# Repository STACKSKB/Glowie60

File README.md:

A Bakeneko60 PCB with RGB underglow LEDs

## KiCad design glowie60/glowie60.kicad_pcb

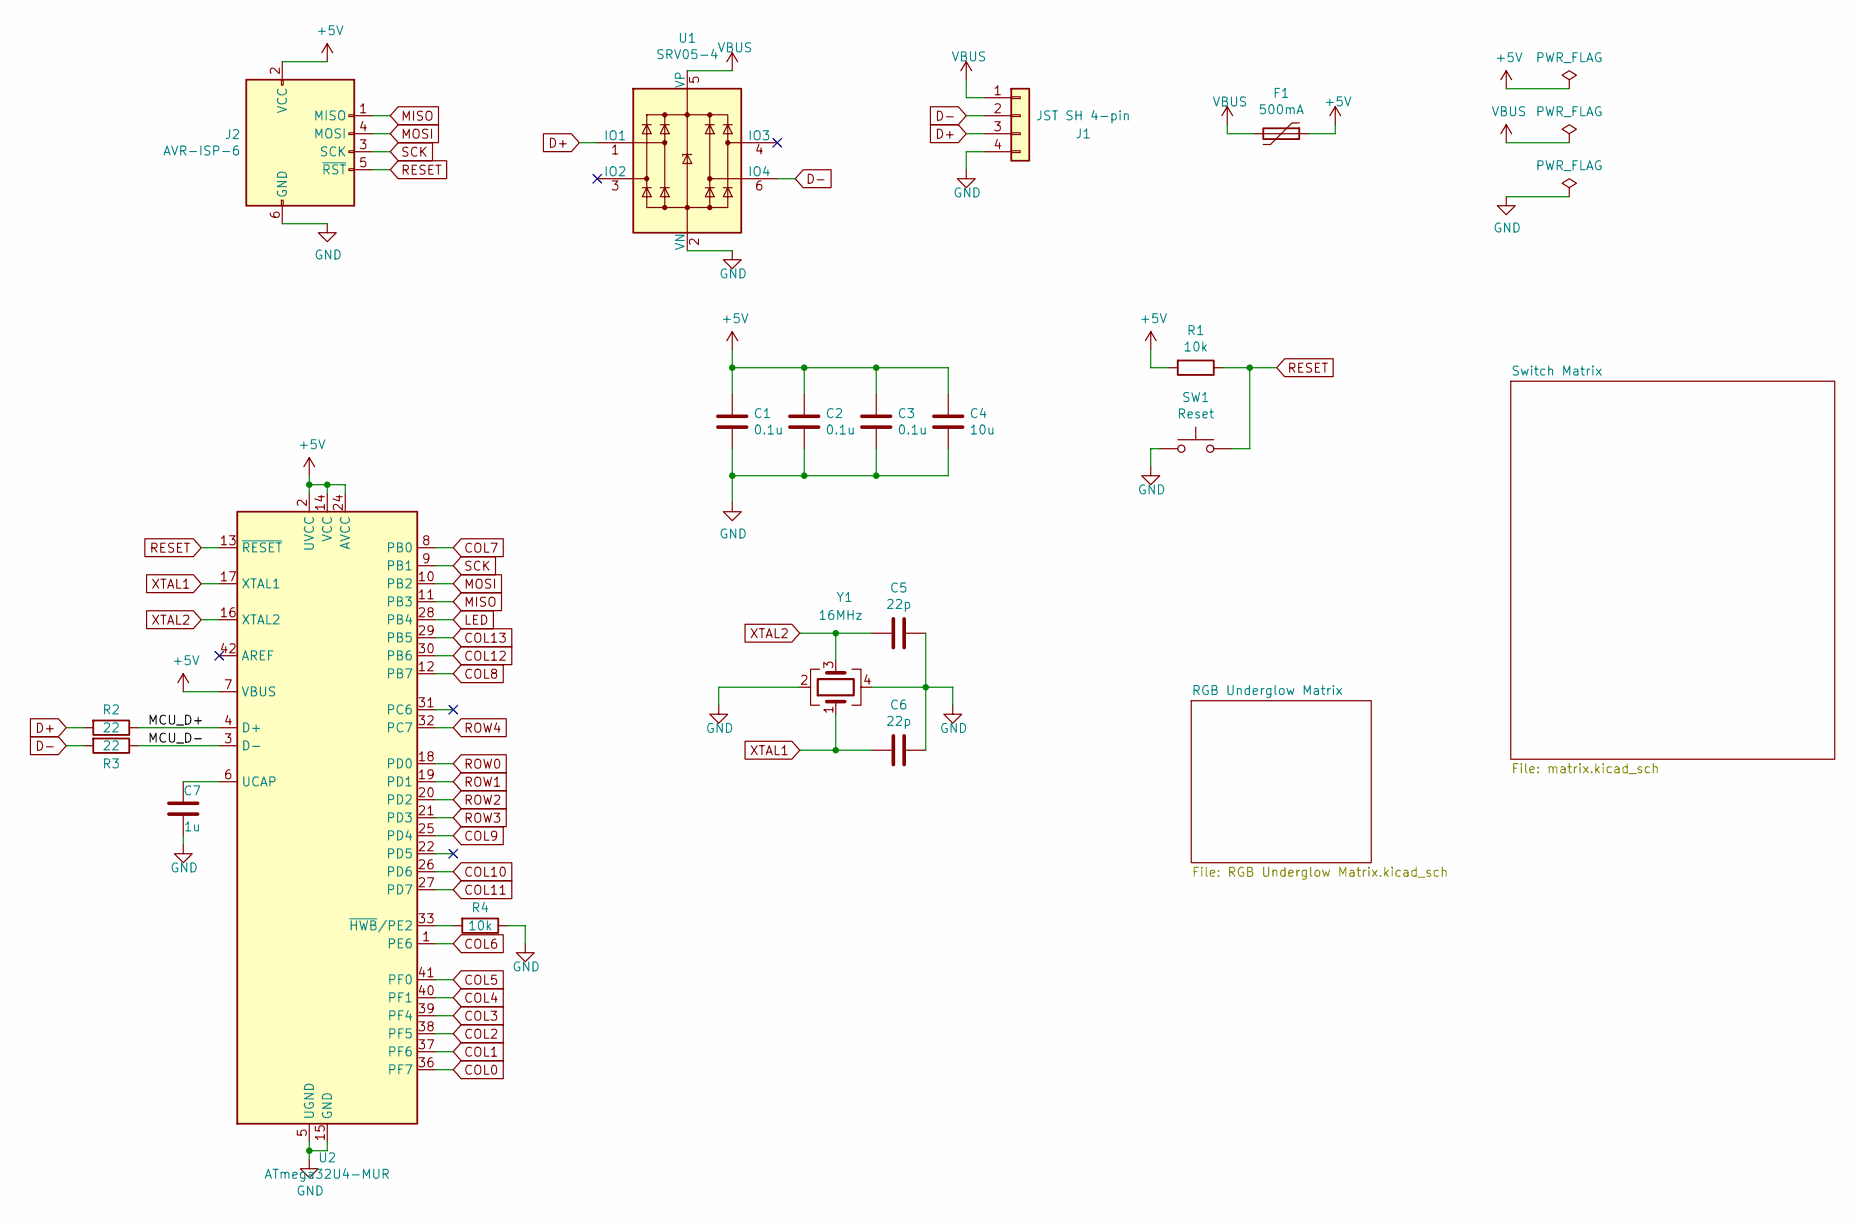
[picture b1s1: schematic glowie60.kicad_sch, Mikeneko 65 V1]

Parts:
C1, C2, C3: 0.1u; C_0805_2012Metric; LCSC Part # C49678
C4: 10u; C_0805_2012Metric; LCSC Part # C15850
C5, C6: 22p; C_0805_2012Metric; LCSC Part # C1804
C7: 1u; C_0805_2012Metric; LCSC Part # C28323
F1: 500mA; Fuse_1206_3216Metric; LCSC Part # C70076
J1: JST SH 4-pin; JST_SH_SM04B-SRSS-TB_1x04-1MP_P1.00mm_Horizontal; LCSC Part # C145956
J2: AVR-ISP-6; ISP
R1, R4: 10k; R_0805_2012Metric; LCSC Part # C17414
R2, R3: 22; R_0805_2012Metric; LCSC Part # C17561
SW1: Reset; SW_SPST_TL3342; LCSC Part # C318884
U1: SRV05-4; SOT-23-6; LCSC Part # C85364
U2: ATmega32U4-MUR; QFN-44-1EP_7x7mm_P0.5mm_EP5.2x5.2mm; LCSC Part # C45874
Y1: 16MHz; Crystal_SMD_3225-4Pin_3.2x2.5mm; LCSC Part # C13738

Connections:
/MCU_D+: R2.1, U2.4 (D+)
/MCU_D-: R3.1, U2.3 (D-)
COL0: U2.36 (PF7); also elsewhere on the board
COL1: U2.37 (PF6); also elsewhere on the board
COL2: U2.38 (PF5); also elsewhere on the board
COL3: U2.39 (PF4); also elsewhere on the board
COL4: U2.40 (PF1); also elsewhere on the board
COL5: U2.41 (PF0); also elsewhere on the board
COL6: U2.1 (PE6); also elsewhere on the board
COL7: U2.8 (PB0); also elsewhere on the board
COL8: U2.12 (PB7); also elsewhere on the board
COL9: U2.25 (PD4); also elsewhere on the board
COL10: U2.26 (PD6); also elsewhere on the board
COL11: U2.27 (PD7); also elsewhere on the board
COL12: U2.30 (PB6); also elsewhere on the board
COL13: U2.29 (PB5); also elsewhere on the board
D+: J1.3, R2.2, U1.1 (IO1)
D-: J1.2, R3.2, U1.6 (IO4)
LED: U2.28 (PB4); also elsewhere on the board
MISO: J2.1 (MISO), U2.11 (PB3)
MOSI: J2.4 (MOSI), U2.10 (PB2)
unnamed: C7.1, U2.6 (UCAP)
unnamed: R4.2, U2.33 (~HWB/PE2)
RESET: J2.5 (~RST), R1.1, SW1.2, U2.13 (~RESET)
ROW0: U2.18 (PD0); also elsewhere on the board
ROW1: U2.19 (PD1); also elsewhere on the board
ROW2: U2.20 (PD2); also elsewhere on the board
ROW3: U2.21 (PD3); also elsewhere on the board
ROW4: U2.32 (PC7); also elsewhere on the board
SCK: J2.3 (SCK), U2.9 (PB1)
VBUS: F1.2, J1.1, U1.5 (VP)
XTAL1: C6.2, U2.17 (XTAL1), Y1.1
XTAL2: C5.2, U2.16 (XTAL2), Y1.3

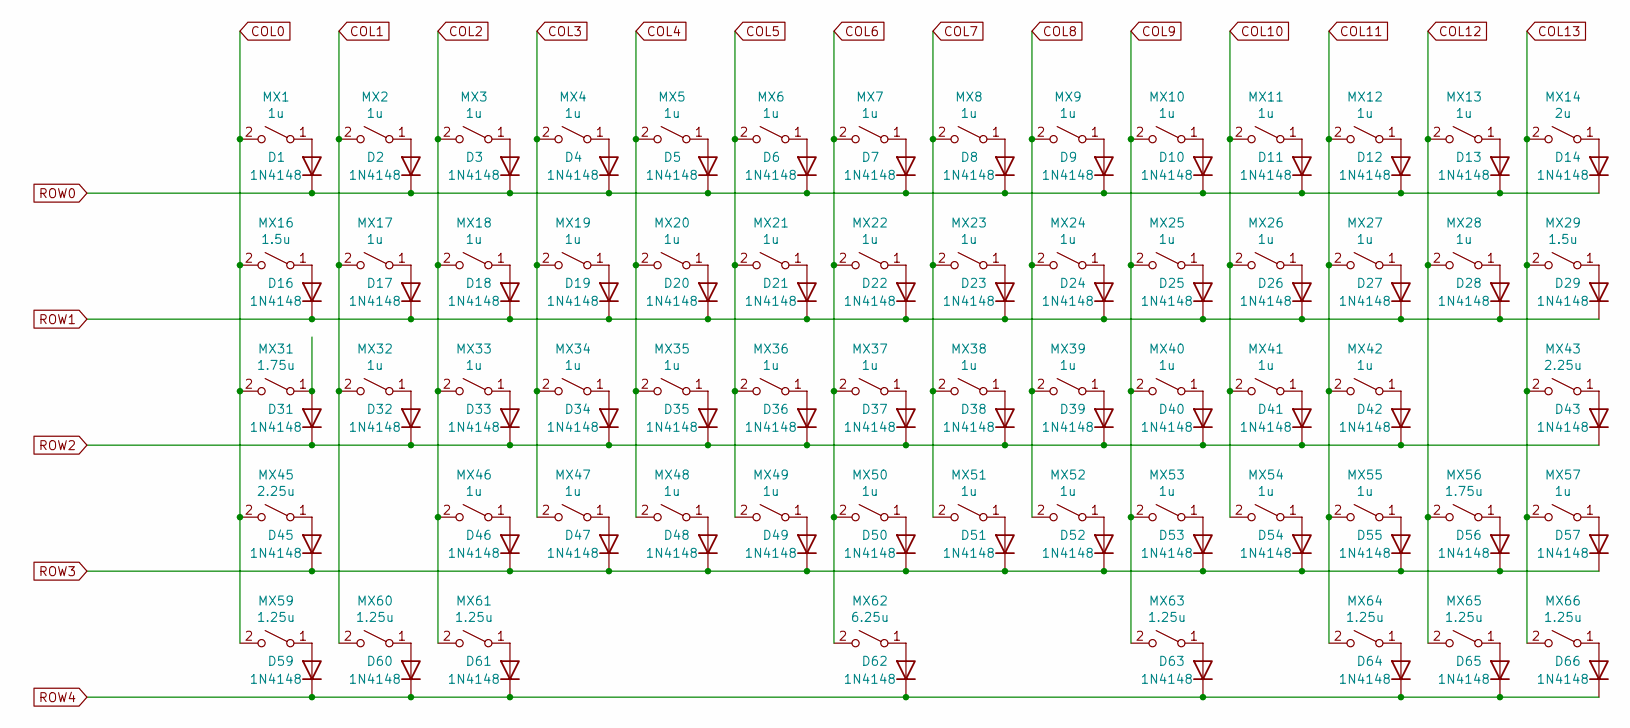
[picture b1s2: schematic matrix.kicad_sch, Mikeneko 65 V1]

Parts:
D1, D2, D3, D4, D5, D6, D7, D8, D9, D10, D11, D12, D13, D14, D16, D17, D18, D19, D20, D21, D22, D23, D24, D25, D26, D27, D28, D29, D31, D32, D33, D34, D35, D36, D37, D38, D39, D40, D41, D42, D43, D45, D46, D47, D48, D49, D50, D51, D52, D53, D54, D55, D56, D57, D59, D60, D61, D62, D63, D64, D65, D66: 1N4148; D_SOD-123; LCSC Part # C81598
MX1, MX2, MX3, MX4, MX5, MX6, MX7, MX8, MX9, MX10, MX11, MX12, MX13, MX17, MX18, MX19, MX20, MX21, MX22, MX23, MX24, MX25, MX26, MX27, MX28, MX32, MX33, MX34, MX35, MX36, MX37, MX38, MX39, MX40, MX41, MX42, MX46, MX47, MX48, MX49, MX50, MX51, MX52, MX53, MX54, MX55, MX57: 1u; MXOnly-1U-Hotswap; LCSC Part # C2803348
MX14: 2u; MXOnly-2U-Hotswap; LCSC Part # C2803348
MX16, MX29: 1.5u; MXOnly-1.5U-Hotswap; LCSC Part # C2803348
MX31, MX56: 1.75u; MXOnly-1.75U-Hotswap; LCSC Part # C2803348
MX43, MX45: 2.25u; MXOnly-2.25U-Hotswap; LCSC Part # C2803348
MX59, MX60, MX61, MX63, MX64, MX65, MX66: 1.25u; MXOnly-1.25U-Hotswap; LCSC Part # C2803348
MX62: 6.25u; MXOnly-6.25U-Hotswap-ReversedStabilizers; LCSC Part # C2803348

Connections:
COL0: MX1.2 (B), MX16.2 (B), MX31.2 (B), MX45.2 (B), MX59.2 (B); also elsewhere on the board
COL1: MX2.2 (B), MX17.2 (B), MX32.2 (B), MX60.2 (B); also elsewhere on the board
COL2: MX3.2 (B), MX18.2 (B), MX33.2 (B), MX46.2 (B), MX61.2 (B); also elsewhere on the board
COL3: MX4.2 (B), MX19.2 (B), MX34.2 (B), MX47.2 (B); also elsewhere on the board
COL4: MX5.2 (B), MX20.2 (B), MX35.2 (B), MX48.2 (B); also elsewhere on the board
COL5: MX6.2 (B), MX21.2 (B), MX36.2 (B), MX49.2 (B); also elsewhere on the board
COL6: MX7.2 (B), MX22.2 (B), MX37.2 (B), MX50.2 (B), MX62.2 (B); also elsewhere on the board
COL7: MX8.2 (B), MX23.2 (B), MX38.2 (B), MX51.2 (B); also elsewhere on the board
COL8: MX9.2 (B), MX24.2 (B), MX39.2 (B), MX52.2 (B); also elsewhere on the board
COL9: MX10.2 (B), MX25.2 (B), MX40.2 (B), MX53.2 (B), MX63.2 (B); also elsewhere on the board
COL10: MX11.2 (B), MX26.2 (B), MX41.2 (B), MX54.2 (B); also elsewhere on the board
COL11: MX12.2 (B), MX27.2 (B), MX42.2 (B), MX55.2 (B), MX64.2 (B); also elsewhere on the board
COL12: MX13.2 (B), MX28.2 (B), MX56.2 (B), MX65.2 (B); also elsewhere on the board
COL13: MX14.2 (B), MX29.2 (B), MX43.2 (B), MX57.2 (B), MX66.2 (B); also elsewhere on the board
unnamed: D1.2 (A), MX1.1 (A)
unnamed: D2.2 (A), MX2.1 (A)
unnamed: D3.2 (A), MX3.1 (A)
unnamed: D4.2 (A), MX4.1 (A)
unnamed: D5.2 (A), MX5.1 (A)
unnamed: D6.2 (A), MX6.1 (A)
unnamed: D7.2 (A), MX7.1 (A)
unnamed: D8.2 (A), MX8.1 (A)
unnamed: D9.2 (A), MX9.1 (A)
unnamed: D10.2 (A), MX10.1 (A)
unnamed: D11.2 (A), MX11.1 (A)
unnamed: D12.2 (A), MX12.1 (A)
unnamed: D13.2 (A), MX13.1 (A)
unnamed: D14.2 (A), MX14.1 (A)
unnamed: D16.2 (A), MX16.1 (A)
unnamed: D17.2 (A), MX17.1 (A)
unnamed: D18.2 (A), MX18.1 (A)
unnamed: D19.2 (A), MX19.1 (A)
unnamed: D20.2 (A), MX20.1 (A)
unnamed: D21.2 (A), MX21.1 (A)
unnamed: D22.2 (A), MX22.1 (A)
unnamed: D23.2 (A), MX23.1 (A)
unnamed: D24.2 (A), MX24.1 (A)
unnamed: D25.2 (A), MX25.1 (A)
unnamed: D26.2 (A), MX26.1 (A)
unnamed: D27.2 (A), MX27.1 (A)
unnamed: D28.2 (A), MX28.1 (A)
unnamed: D29.2 (A), MX29.1 (A)
unnamed: D31.2 (A), MX31.1 (A)
unnamed: D32.2 (A), MX32.1 (A)
unnamed: D33.2 (A), MX33.1 (A)
unnamed: D34.2 (A), MX34.1 (A)
unnamed: D35.2 (A), MX35.1 (A)
unnamed: D36.2 (A), MX36.1 (A)
unnamed: D37.2 (A), MX37.1 (A)
unnamed: D38.2 (A), MX38.1 (A)
unnamed: D39.2 (A), MX39.1 (A)
unnamed: D40.2 (A), MX40.1 (A)
unnamed: D41.2 (A), MX41.1 (A)
unnamed: D42.2 (A), MX42.1 (A)
unnamed: D43.2 (A), MX43.1 (A)
unnamed: D45.2 (A), MX45.1 (A)
unnamed: D46.2 (A), MX46.1 (A)
unnamed: D47.2 (A), MX47.1 (A)
unnamed: D48.2 (A), MX48.1 (A)
unnamed: D49.2 (A), MX49.1 (A)
unnamed: D50.2 (A), MX50.1 (A)
unnamed: D51.2 (A), MX51.1 (A)
unnamed: D52.2 (A), MX52.1 (A)
unnamed: D53.2 (A), MX53.1 (A)
unnamed: D54.2 (A), MX54.1 (A)
unnamed: D55.2 (A), MX55.1 (A)
unnamed: D56.2 (A), MX56.1 (A)
unnamed: D57.2 (A), MX57.1 (A)
unnamed: D59.2 (A), MX59.1 (A)
unnamed: D60.2 (A), MX60.1 (A)
unnamed: D61.2 (A), MX61.1 (A)
unnamed: D62.2 (A), MX62.1 (A)
unnamed: D63.2 (A), MX63.1 (A)
unnamed: D64.2 (A), MX64.1 (A)
unnamed: D65.2 (A), MX65.1 (A)
unnamed: D66.2 (A), MX66.1 (A)
ROW0: D1.1 (K), D2.1 (K), D3.1 (K), D4.1 (K), D5.1 (K), D6.1 (K), D7.1 (K), D8.1 (K), D9.1 (K), D10.1 (K), D11.1 (K), D12.1 (K), D13.1 (K), D14.1 (K); also elsewhere on the board
ROW1: D16.1 (K), D17.1 (K), D18.1 (K), D19.1 (K), D20.1 (K), D21.1 (K), D22.1 (K), D23.1 (K), D24.1 (K), D25.1 (K), D26.1 (K), D27.1 (K), D28.1 (K), D29.1 (K); also elsewhere on the board
ROW2: D31.1 (K), D32.1 (K), D33.1 (K), D34.1 (K), D35.1 (K), D36.1 (K), D37.1 (K), D38.1 (K), D39.1 (K), D40.1 (K), D41.1 (K), D42.1 (K), D43.1 (K); also elsewhere on the board
ROW3: D45.1 (K), D46.1 (K), D47.1 (K), D48.1 (K), D49.1 (K), D50.1 (K), D51.1 (K), D52.1 (K), D53.1 (K), D54.1 (K), D55.1 (K), D56.1 (K), D57.1 (K); also elsewhere on the board
ROW4: D59.1 (K), D60.1 (K), D61.1 (K), D62.1 (K), D63.1 (K), D64.1 (K), D65.1 (K), D66.1 (K); also elsewhere on the board

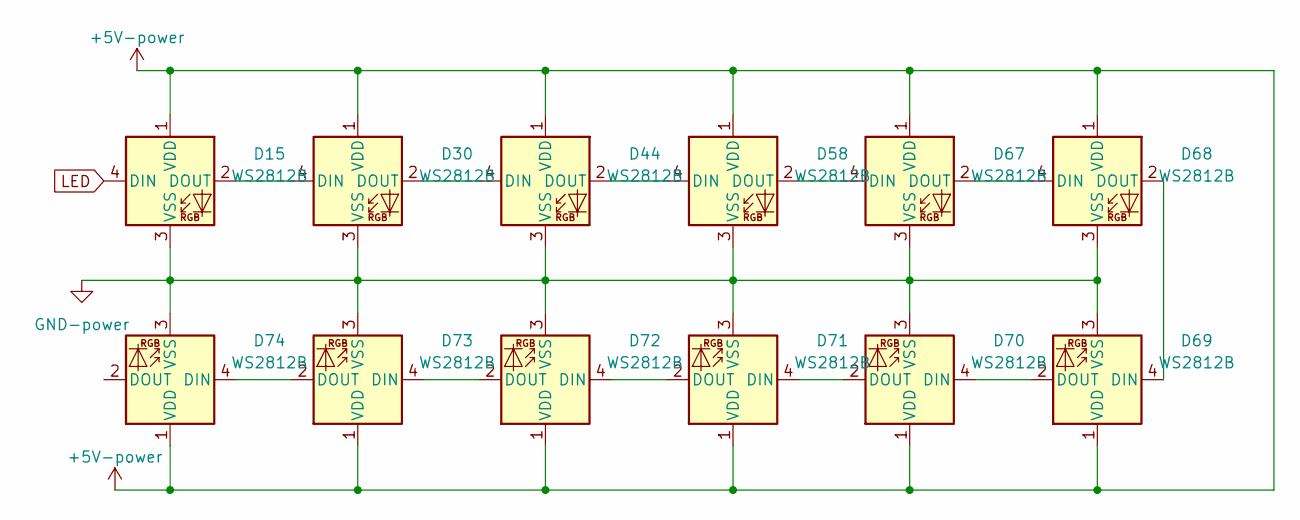
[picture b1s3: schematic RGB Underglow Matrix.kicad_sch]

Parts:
D15, D30, D44, D58, D67, D68, D69, D70, D71, D72, D73, D74: WS2812B; LED_WS2812B_PLCC4_5.0x5.0mm_P3.2mm

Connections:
LED: D15.4 (DIN); also elsewhere on the board
unnamed: D15.2 (DOUT), D30.4 (DIN)
unnamed: D30.2 (DOUT), D44.4 (DIN)
unnamed: D44.2 (DOUT), D58.4 (DIN)
unnamed: D58.2 (DOUT), D67.4 (DIN)
unnamed: D67.2 (DOUT), D68.4 (DIN)
unnamed: D68.2 (DOUT), D69.4 (DIN)
unnamed: D69.2 (DOUT), D70.4 (DIN)
unnamed: D70.2 (DOUT), D71.4 (DIN)
unnamed: D71.2 (DOUT), D72.4 (DIN)
unnamed: D72.2 (DOUT), D73.4 (DIN)
unnamed: D73.2 (DOUT), D74.4 (DIN)

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
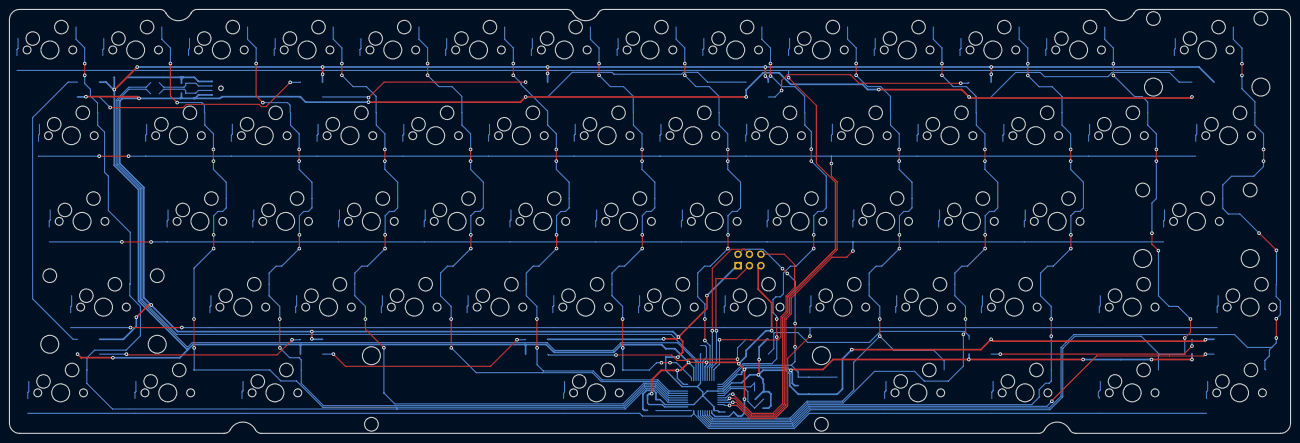
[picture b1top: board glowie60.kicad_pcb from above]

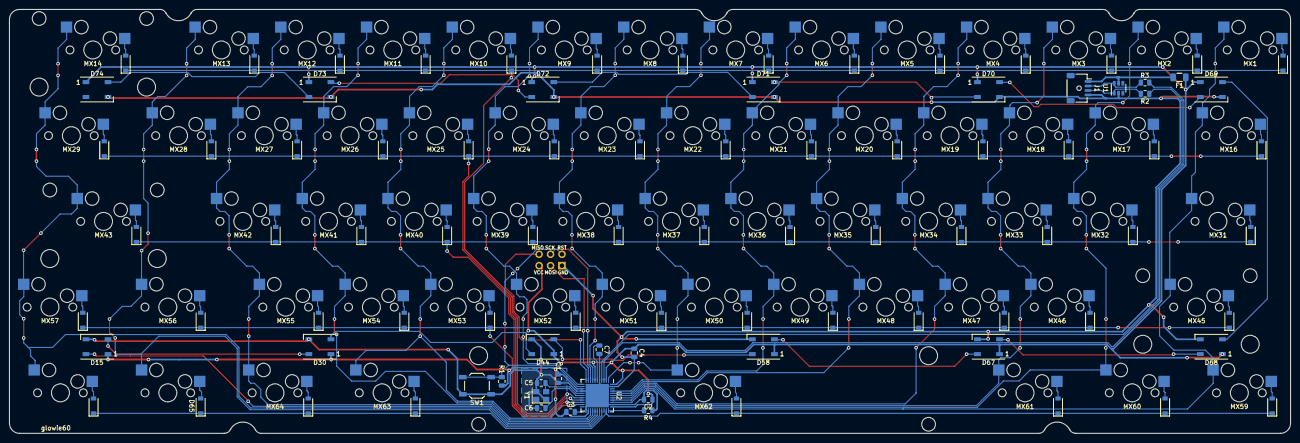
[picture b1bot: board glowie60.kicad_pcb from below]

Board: 2 copper layers, 284.7 x 94.2 mm, 154 parts (91 on the bottom side), 108 nets.

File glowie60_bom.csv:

Id;Designator;Footprint;Quantity;Designation;Supplier and ref
1;MX1,MX2,MX3,MX4,MX5,MX6,MX7,MX9,MX10,MX11,MX12,MX13,MX17,MX18,MX19,MX20,MX22,MX23,MX24,MX25,MX26,MX27,MX28,MX32,MX33,MX34,MX35,MX36,MX37,MX38,MX39,MX40,MX41,MX42,MX46,MX47,MX48,MX49,MX50,MX51,MX52,MX53,MX54,MX55,MX57,MX8,MX21;MXOnly-1U-Hotswap;47;1u;Hotswap Socket
2;MX14;MXOnly-2U-Hotswap;1;2u;Hotswap Socket
3;MX16,MX29;MXOnly-1.5U-Hotswap;2;1.5u;Hotswap Socket
4;MX31,MX56;MXOnly-1.75U-Hotswap;2;1.75u;Hotswap Socket
5;MX43,MX45;MXOnly-2.25U-Hotswap;2;2.25u;Hotswap Socket
6;MX63,MX65,MX64,MX59,MX60,MX61,MX66;MXOnly-1.25U-Hotswap;7;1.25u;Hotswap Socket
7;MX62;MXOnly-6.25U-Hotswap-ReversedStabilizers;1;6.25u;Hotswap Socket
9;J1;JST_SH_SM04B-SRSS-TB_1x04-1MP_P1.00mm_Horizontal;1;JST SH 4-pin;LCSC #C145956
10;R2,R3;R_0805_2012Metric;2;22;LCSC #C17414
11;SW1;SW_SPST_TL3342;1;Reset;LCSC #C318884
12;C5,C6;C_0805_2012Metric;2;22p;LCSC #C1804
13;C3,C1,C2;C_0805_2012Metric;3;0.1u;LCSC #C49678
14;Y1;Crystal_SMD_3225-4Pin_3.2x2.5mm;1;16MHz;LCSC #C13738
15;R1,R4;R_0805_2012Metric;2;10k;LCSC #C17561
16;D1,D2,D3,D4,D5,D6,D7,D8,D9,D10,D11,D12,D14,D16,D17,D18,D19,D20,D21,D22,D23,D24,D25,D26,D27,D28,D29,D31,D32,D33,D34,D36,D37,D38,D39,D40,D41,D42,D43,D45,D46,D47,D48,D49,D50,D51,D52,D53,D54,D55,D56,D57,D59,D60,D61,D62,D64,D13,D35,D63,D66,D65;D_SOD-123;62;1N4148;LCSC #C81598
17;C7;C_0805_2012Metric;1;1u;LCSC #C28323
18;U1;SOT-23-6;1;SRV05-4;LCSC #C85364
19;U2;QFN-44-1EP_7x7mm_P0.5mm_EP5.2x5.2mm;1;ATmega32U4-MUR;LCSC #C45874
20;F1;Fuse_1206_3216Metric;1;500mA;LCSC #C70076
21;C4;C_0805_2012Metric;1;10u;LCSC #C15850
22;D71,D44,D58,D72,D15,D68,D30,D74,D67,D69,D70,D73;LED_WS2812B_PLCC4_5.0x5.0mm_P3.2mm;12;WS2812B;LCSC #C2874885

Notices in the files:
glowie60/glowie60.kicad_sch:
Copyright © 2020 kkatano
MIT License
